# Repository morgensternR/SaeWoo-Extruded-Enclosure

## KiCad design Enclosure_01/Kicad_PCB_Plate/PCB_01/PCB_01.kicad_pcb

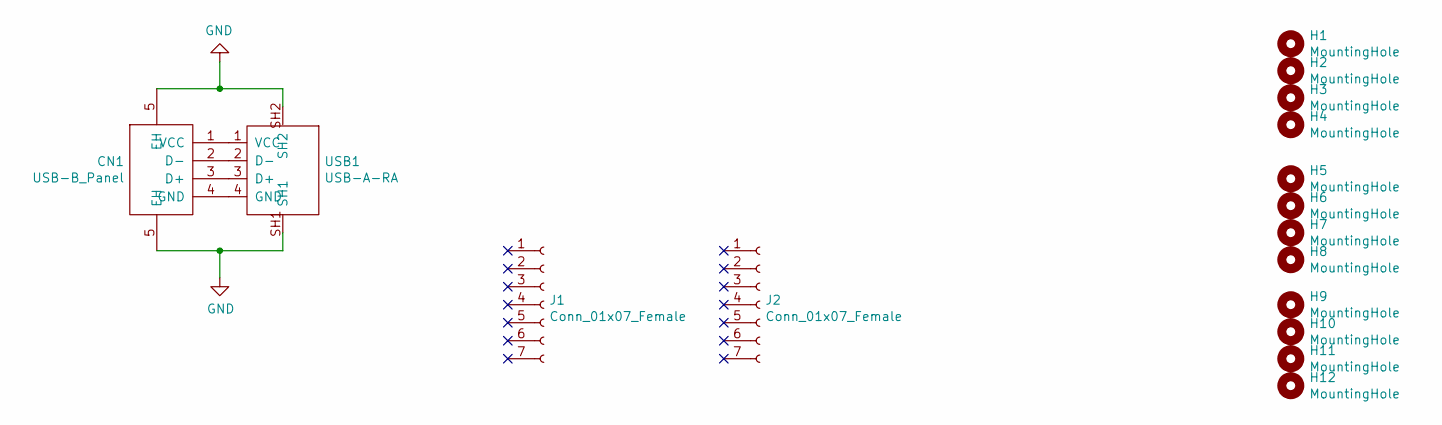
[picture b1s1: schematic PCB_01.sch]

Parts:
CN1: USB-B_Panel; USB-B_TH_BF90; LCSC C86462
H1, H2, H3, H4, H5, H6, H7, H8, H9, H10, H11, H12: MountingHole; MountingHole_3.5mm_Pad
J1, J2: Conn_01x07_Female; 1x7_2.54mm_FemaleHeader; LCSC C358721
USB1: USB-A-RA; USB-A-TH__USB-AF-90; LCSC C2345

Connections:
GND: CN1.5 (EH), USB1.SH1, USB1.SH2
unnamed: CN1.1 (VCC), USB1.1 (VCC)
unnamed: CN1.2 (D-), USB1.2 (D-)
unnamed: CN1.3 (D+), USB1.3 (D+)
unnamed: CN1.4 (GND), USB1.4 (GND)

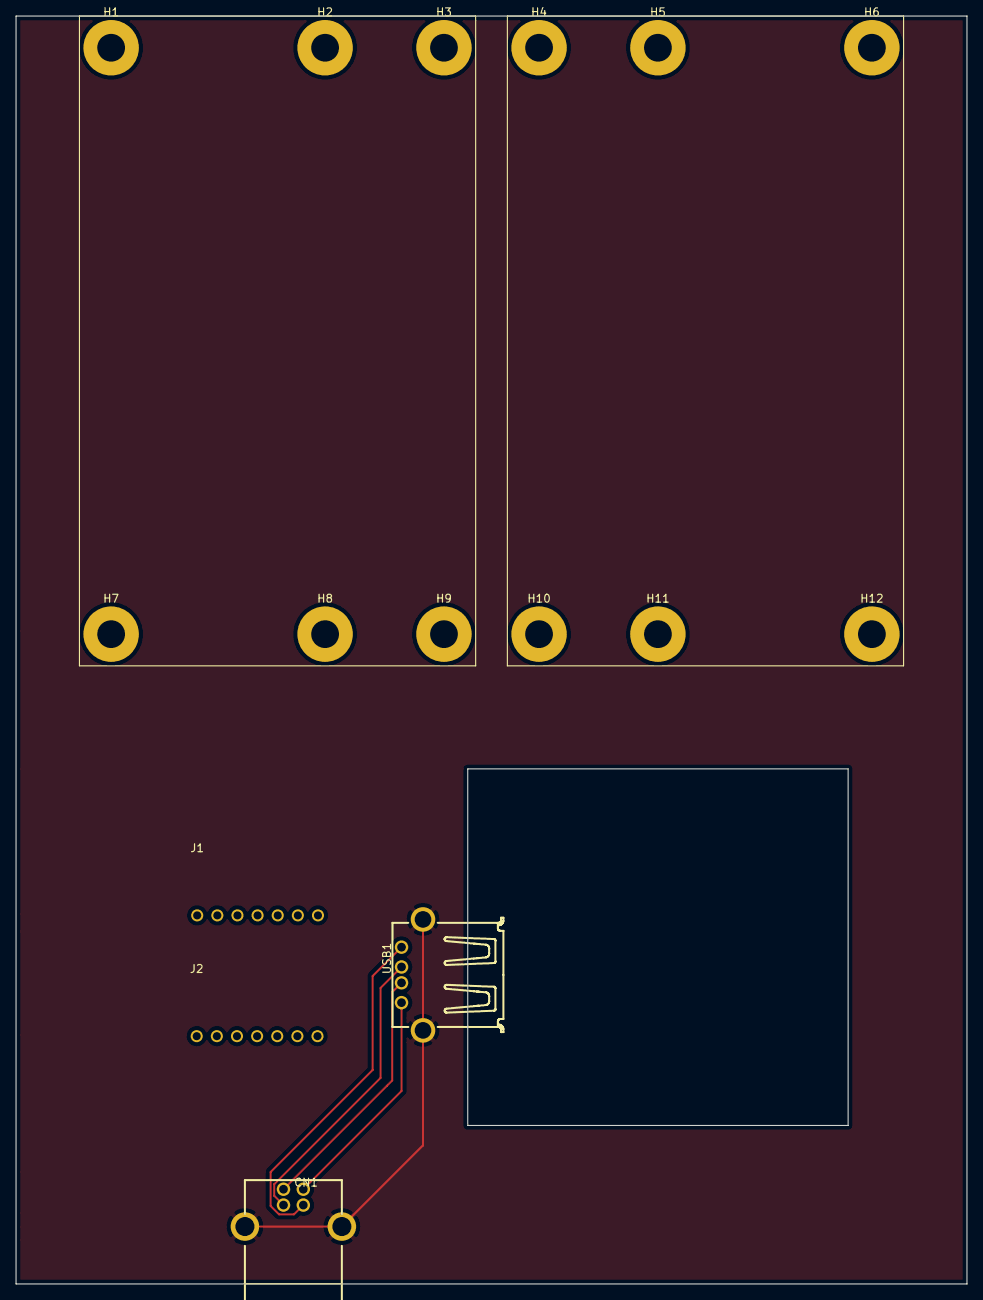
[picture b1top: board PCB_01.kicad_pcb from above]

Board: 2 copper layers, 120.0 x 160.0 mm, 16 parts (0 on the bottom side), 5 nets.

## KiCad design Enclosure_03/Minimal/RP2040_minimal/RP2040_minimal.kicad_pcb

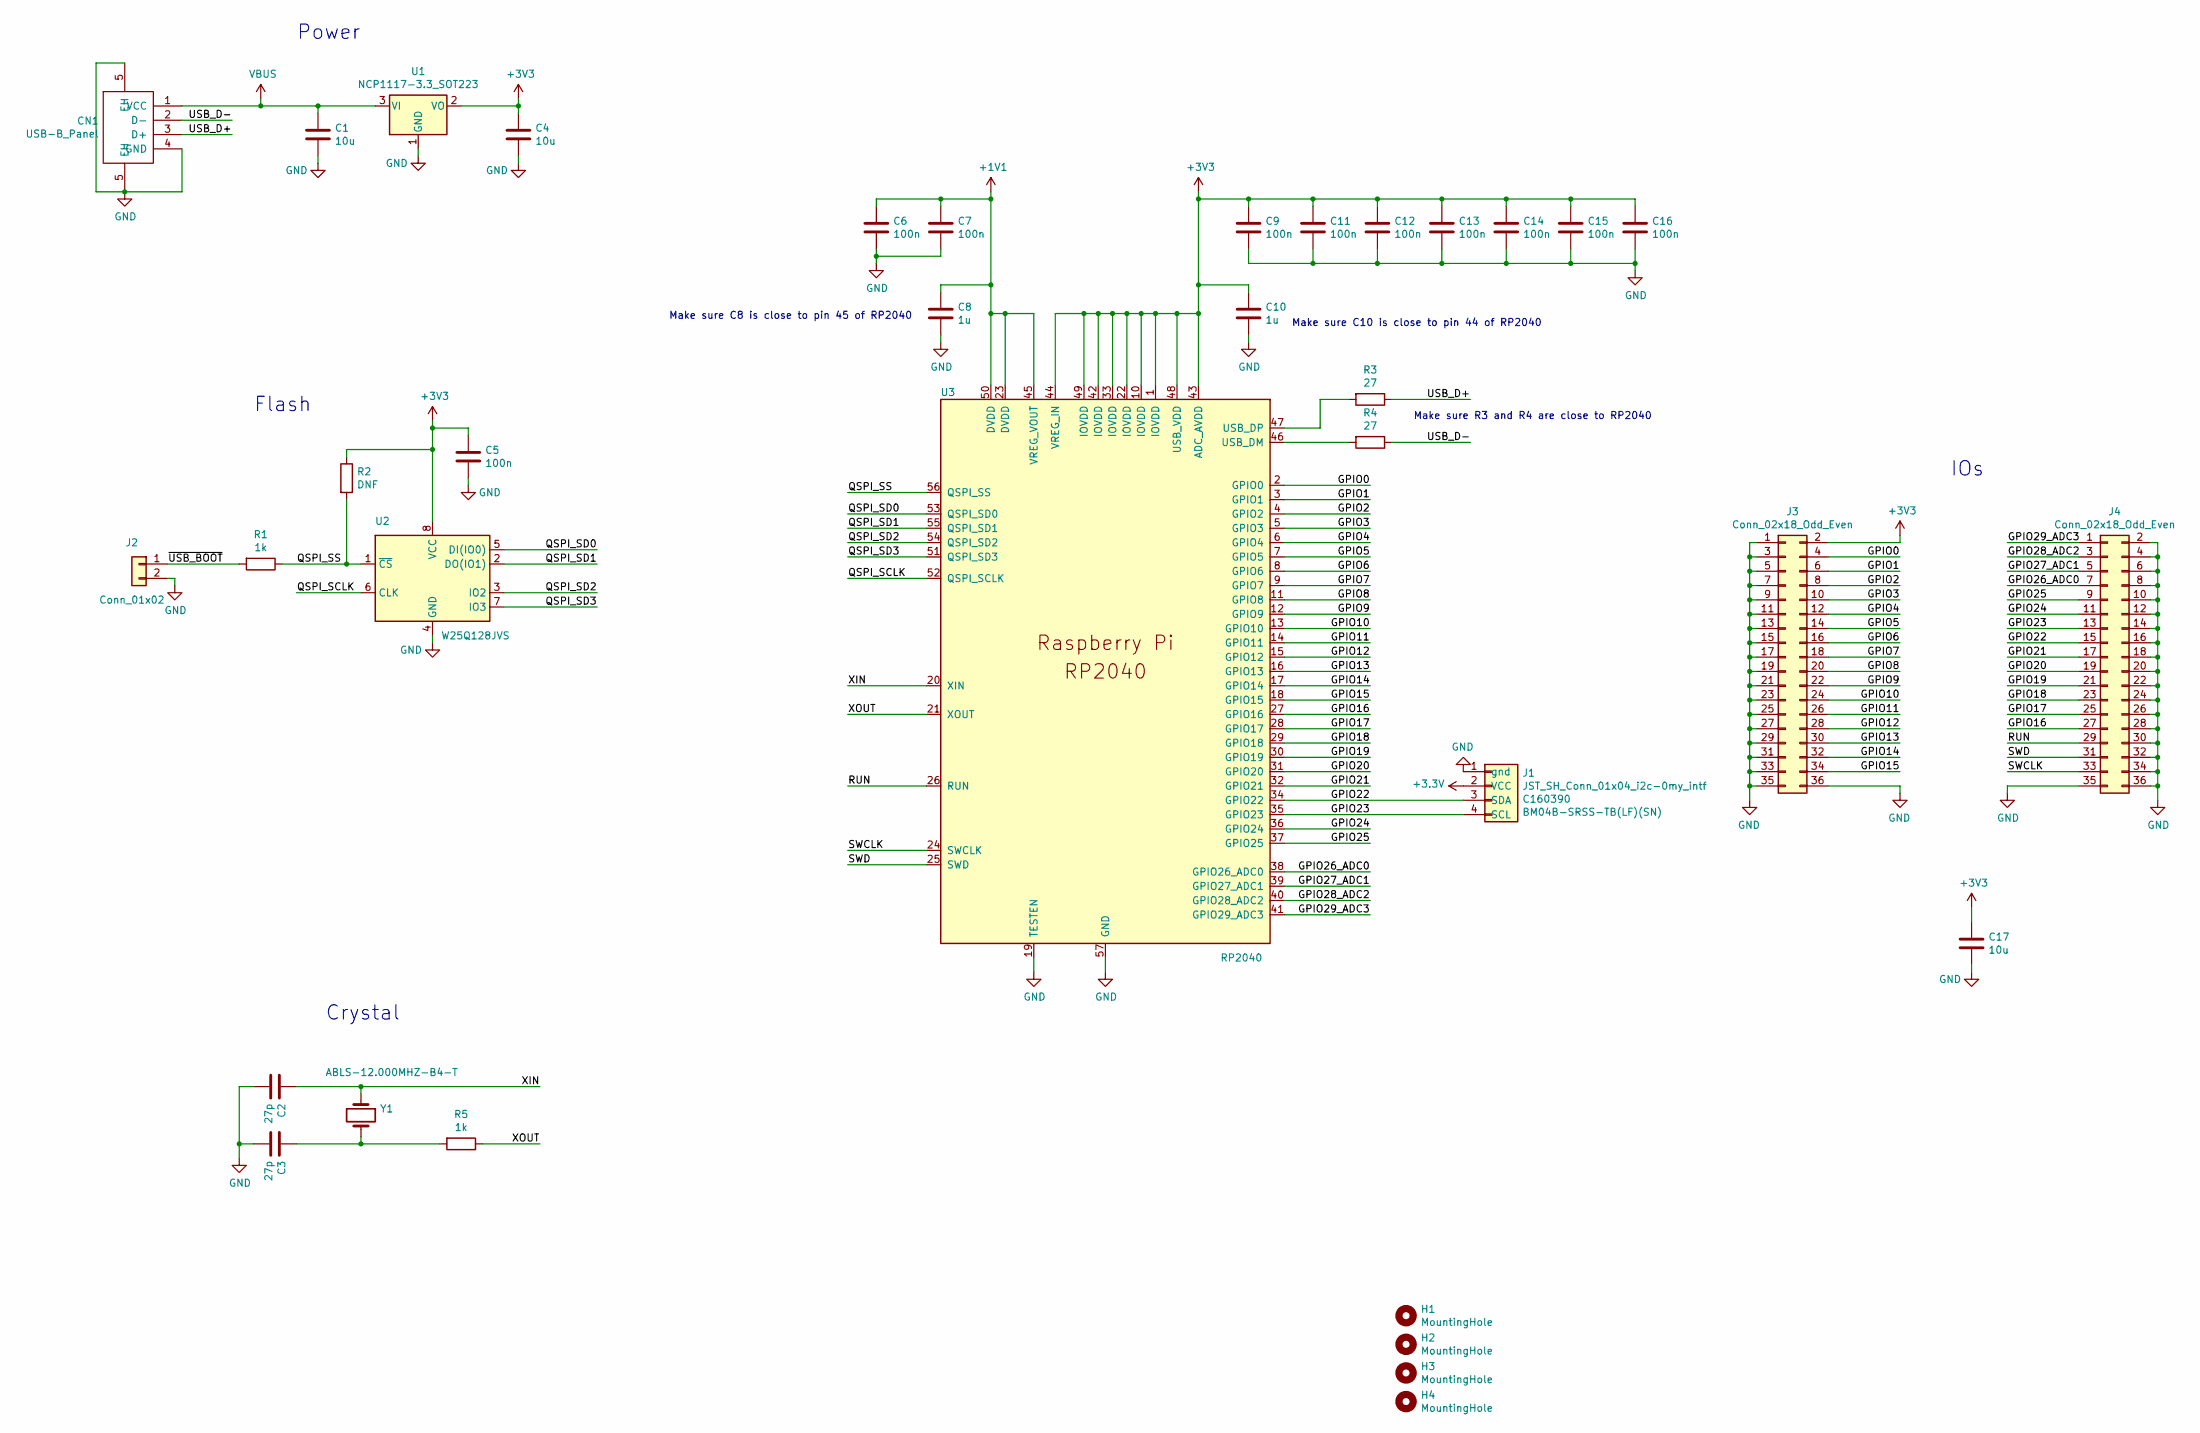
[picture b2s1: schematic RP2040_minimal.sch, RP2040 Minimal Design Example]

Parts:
C1, C4, C17: 10u; C_0805_2012Metric
C2, C3: 27p; C_0402_1005Metric
C5, C6, C7, C9, C11, C12, C13, C14, C15, C16: 100n; C_0402_1005Metric
C8, C10: 1u; C_0402_1005Metric
CN1: USB-B_Panel; USB-B_TH_BF90
H1, H2, H3, H4: MountingHole; MountingHole_2.7mm_M2.5
J1: JST_SH_Conn_01x04_i2c-0my_intf; JST_SH_BM04B-SRSS-TB_1x04-1MP_P1.00mm_Vertical; MPN BM04B-SRSS-TB(LF)(SN); LCSC C160390
J2: Conn_01x02; PinHeader_1x02_P2.54mm_Vertical
J3, J4: Conn_02x18_Odd_Even; PinHeader_2x18_P2.54mm_Vertical
R1, R5: 1k; C_0402_1005Metric
R2: DNF; C_0402_1005Metric
R3, R4: 27; C_0402_1005Metric
U1: NCP1117-3.3_SOT223; SOT-223-3_TabPin2
U2: W25Q128JVS; SOIC-8_5.23x5.23mm_P1.27mm
U3: RP2040; RP2040-QFN-56
Y1: ABLS-12.000MHZ-B4-T; Crystal_SMD_HC49-US

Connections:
+1V1: C6.1, C7.1, C8.1, U3.23 (DVDD), U3.45 (VREG_VOUT), U3.50 (DVDD)
/GPIO0: J3.4, U3.2 (GPIO0)
/GPIO1: J3.6, U3.3 (GPIO1)
/GPIO2: J3.8, U3.4 (GPIO2)
/GPIO3: J3.10, U3.5 (GPIO3)
/GPIO4: J3.12, U3.6 (GPIO4)
/GPIO5: J3.14, U3.7 (GPIO5)
/GPIO6: J3.16, U3.8 (GPIO6)
/GPIO7: J3.18, U3.9 (GPIO7)
/GPIO8: J3.20, U3.11 (GPIO8)
/GPIO9: J3.22, U3.12 (GPIO9)
/GPIO10: J3.24, U3.13 (GPIO10)
/GPIO11: J3.26, U3.14 (GPIO11)
/GPIO12: J3.28, U3.15 (GPIO12)
/GPIO13: J3.30, U3.16 (GPIO13)
/GPIO14: J3.32, U3.17 (GPIO14)
/GPIO15: J3.34, U3.18 (GPIO15)
/GPIO16: J4.27, U3.27 (GPIO16)
/GPIO17: J4.25, U3.28 (GPIO17)
/GPIO18: J4.23, U3.29 (GPIO18)
/GPIO19: J4.21, U3.30 (GPIO19)
/GPIO20: J4.19, U3.31 (GPIO20)
/GPIO21: J4.17, U3.32 (GPIO21)
/GPIO22: J1.3 (SDA), J4.15, U3.34 (GPIO22)
/GPIO23: J1.4 (SCL), J4.13, U3.35 (GPIO23)
/GPIO24: J4.11, U3.36 (GPIO24)
/GPIO25: J4.9, U3.37 (GPIO25)
/GPIO26_ADC0: J4.7, U3.38 (GPIO26_ADC0)
/GPIO27_ADC1: J4.5, U3.39 (GPIO27_ADC1)
/GPIO28_ADC2: J4.3, U3.40 (GPIO28_ADC2)
/GPIO29_ADC3: J4.1, U3.41 (GPIO29_ADC3)
/QSPI_SCLK: U2.6 (CLK), U3.52 (QSPI_SCLK)
/QSPI_SD0: U2.5 (DI(IO0)), U3.53 (QSPI_SD0)
/QSPI_SD1: U2.2 (DO(IO1)), U3.55 (QSPI_SD1)
/QSPI_SD2: U2.3 (IO2), U3.54 (QSPI_SD2)
/QSPI_SD3: U2.7 (IO3), U3.51 (QSPI_SD3)
/QSPI_SS: R1.1, R2.2, U2.1 (~CS), U3.56 (QSPI_SS)
/RUN: J4.29, U3.26 (RUN)
/SWCLK: J4.33, U3.24 (SWCLK)
/SWD: J4.31, U3.25 (SWD)
/USB_D+: CN1.3 (D+), R3.1
/USB_D-: CN1.2 (D-), R4.1
/XIN: C2.1, U3.20 (XIN), Y1.1
/XOUT: R5.1, U3.21 (XOUT)
/~USB_BOOT: J2.1, R1.2
GND: C1.2, C2.2, C3.2, C4.2, C5.2, C6.2, C7.2, C8.2, C9.2, C10.2, C11.2, C12.2, C13.2, C14.2, C15.2, C16.2, C17.2, CN1.4 (GND), CN1.5 (EH), J1.1 (gnd), J2.2, J3.1, J3.3, J3.5, J3.7, J3.9, J3.11, J3.13, J3.15, J3.17, J3.19, J3.21, J3.23, J3.25, J3.27, J3.29, J3.31, J3.33, J3.35, J3.36, J4.2, J4.4, J4.6, J4.8, J4.10, J4.12, J4.14, J4.16, J4.18, J4.20, J4.22, J4.24, J4.26, J4.28, J4.30, J4.32, J4.34, J4.35, J4.36, U1.1 (GND), U2.4 (GND), U3.19 (TESTEN), U3.57 (GND)
unnamed: C3.1, R5.2, Y1.2
unnamed: R3.2, U3.47 (USB_DP)
unnamed: R4.2, U3.46 (USB_DM)
VBUS: C1.1, CN1.1 (VCC), U1.3 (VI)

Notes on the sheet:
Make sure C10 is close to pin 44 of RP2040
Make sure C8 is close to pin 45 of RP2040
Crystal
Flash
Power
IOs
Make sure R3 and R4 are close to RP2040

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
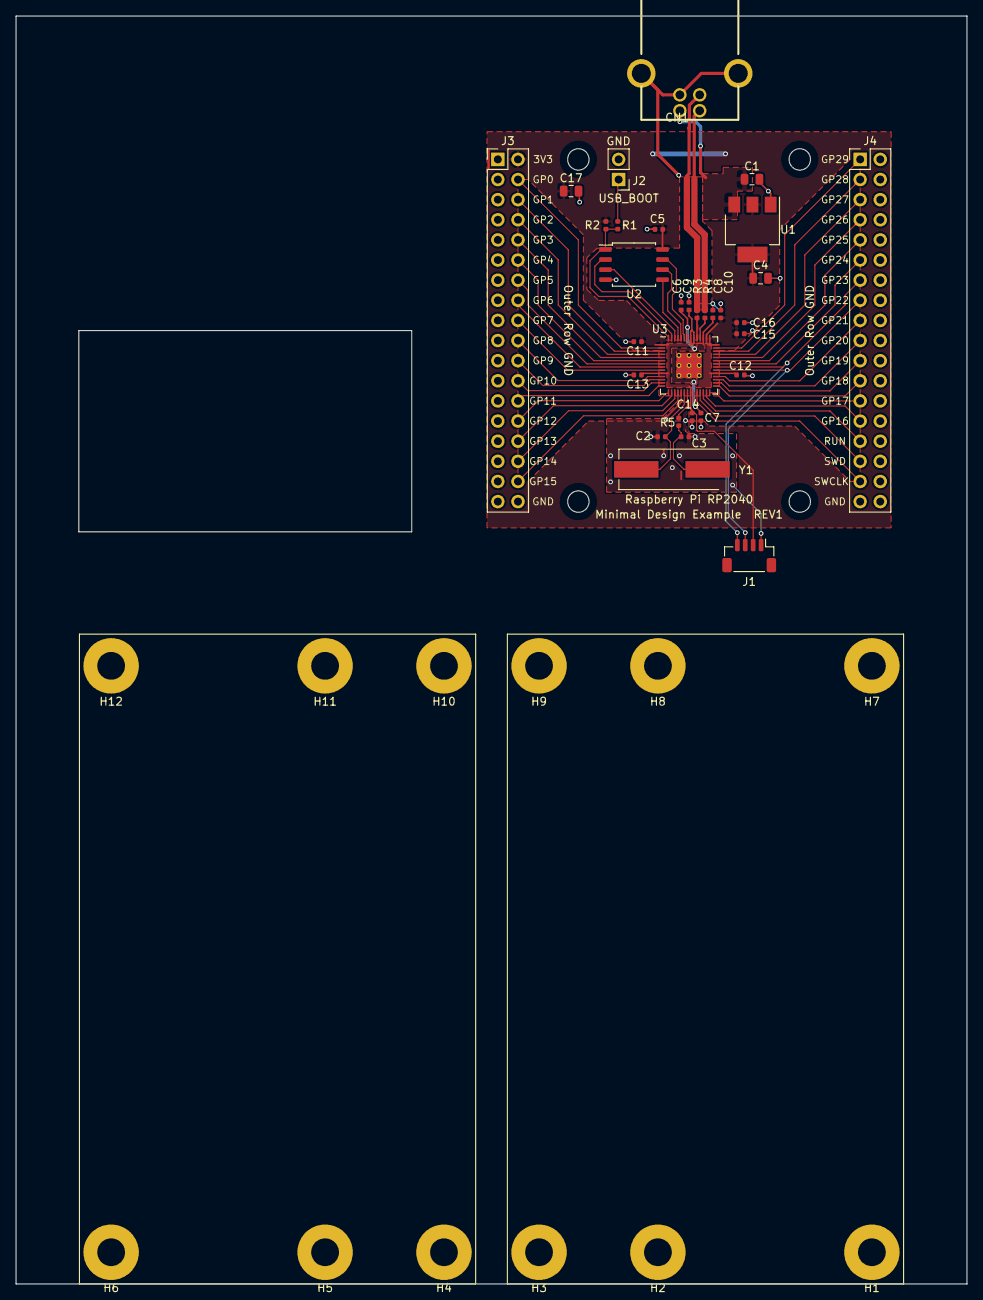
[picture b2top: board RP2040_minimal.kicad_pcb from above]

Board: 2 copper layers, 120.0 x 160.0 mm, 47 parts (0 on the bottom side), 51 nets.

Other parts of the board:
H1#2, H2#2, H3#2, H4#2: MountingHole; MountingHole_2.7mm_M2.5
H5, H6, H7, H8, H9, H10, H11, H12: MountingHole; MountingHole_3.5mm_Pad

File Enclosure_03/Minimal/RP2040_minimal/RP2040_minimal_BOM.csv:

"Id";"Designator";"Package";"Quantity";"Designation";"Supplier and ref";
1;"CN1";"USB-B_TH_BF90";1;"USB-B_Panel";;;
2;"H12,H11,H9,H10,H8,H7,H5,H3,H2,H6,H4,H1";"MountingHole_3.5mm_Pad";12;"MountingHole";;;
3;"J1";"JST_SH_BM04B-SRSS-TB_1x04-1MP_P1.00mm_Vertical";1;"JST_SH_Conn_01x04_i2c-0my_intf";;;
4;"C17,C4,C1";"C_0805_2012Metric";3;"10u";;;
5;"Y1";"Crystal_SMD_HC49-US";1;"ABLS-12.000MHZ-B4-T";;;
6;"U3";"RP2040-QFN-56";1;"RP2040";;;
7;"R5,R1";"C_0402_1005Metric";2;"1k";;;
8;"H4,H3,H2,H1";"MountingHole_2.7mm_M2.5";4;"MountingHole";;;
9;"R4,R3";"C_0402_1005Metric";2;"27";;;
10;"R2";"C_0402_1005Metric";1;"DNF";;;
11;"C16,C15,C14,C13,C12,C11,C9,C7,C6,C5";"C_0402_1005Metric";10;"100n";;;
12;"C10,C8";"C_0402_1005Metric";2;"1u";;;
13;"C3,C2";"C_0402_1005Metric";2;"27p";;;
14;"U2";"SOIC-8_5.23x5.23mm_P1.27mm";1;"W25Q128JVS";;;
15;"U1";"SOT-223-3_TabPin2";1;"NCP1117-3.3_SOT223";;;
16;"J4,J3";"PinHeader_2x18_P2.54mm_Vertical";2;"Conn_02x18_Odd_Even";;;
17;"J2";"PinHeader_1x02_P2.54mm_Vertical";1;"Conn_01x02";;;

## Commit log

2022-01-10 Update PCB_02 files
2022-01-10 Added KiCAD Panels / Updated CAD
    Front and back panels made in KiCAD and checked for fitment in CAD
2022-01-10 Update Gerber
2022-01-11 Added masks to Kicad Front/back plates
2022-01-12 Updated mounting holes for Copper Plane and Gerber
